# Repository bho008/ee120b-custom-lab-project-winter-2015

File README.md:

# ee120b-custom-lab-project-winter-2015
BACKUP EVERYTHING 

Brian Ho's EE120B Custom Lab Project Winter 2015
bho008@ucr.edu

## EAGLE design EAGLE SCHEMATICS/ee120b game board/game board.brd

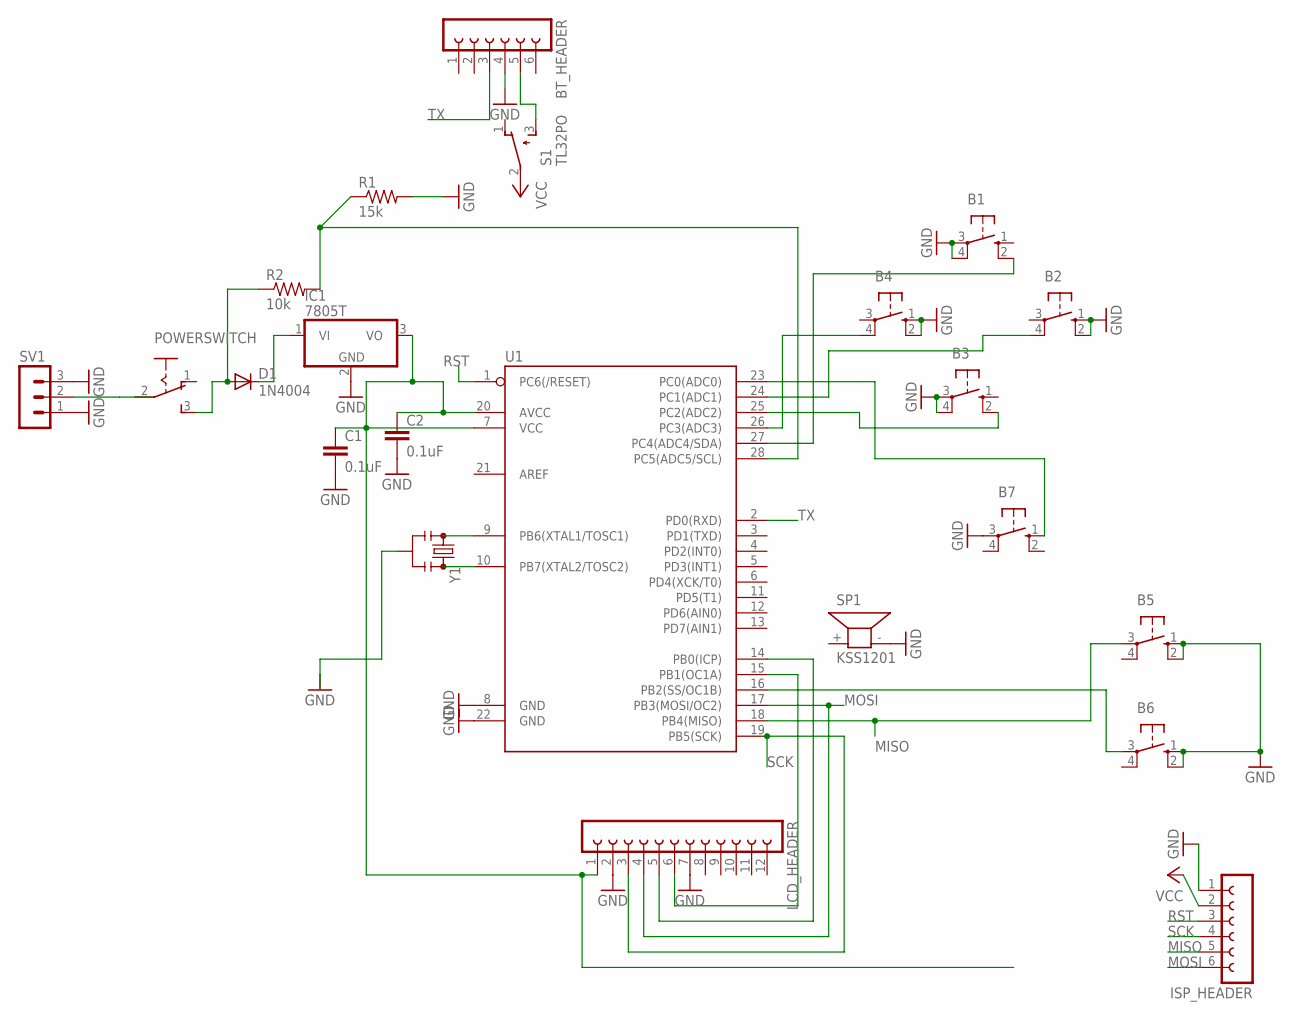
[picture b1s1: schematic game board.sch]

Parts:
B1, B2, B3, B4, B5, B6, B7: 10-XX; B3F-10XX
BT_HEADER: FE06W
C1, C2: 0.1uF; 0603-CAP
D1: 1N4004; DO41-10
IC1: 7805T; TO220H
ISP_HEADER: FE06W
LCD_HEADER: FE12W
POWERSWITCH: M251
R1: 15k; 0204/7
R2: 10k; 0204/7
S1: TL32PO; TL3XPO
SP1: KSS1201
SV1: MA03-1
U1: ATMEGA328P_PDIP; DIL28-3
Y1: RESONATORPTH; RESONATOR-PTH

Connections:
GND: B1.3, B1.4 (P1), B2.1 (S), B2.2 (S1), B3.3, B3.4 (P1), B4.1 (S), B4.2 (S1), B5.1 (S), B5.2 (S1), B6.1 (S), B6.2 (S1), B7.3, BT_HEADER.4, C1.2, C2.2, IC1.2 (GND), ISP_HEADER.1, LCD_HEADER.2, LCD_HEADER.7, R1.2, SP1.- (2), SV1.1, SV1.3, U1.8 (GND), U1.22 (GND), Y1.2
MISO: B5.3, ISP_HEADER.5, U1.18 (PB4(MISO))
MOSI: ISP_HEADER.6, LCD_HEADER.4, U1.17 (PB3(MOSI/OC2))
unnamed: D1.C, IC1.1 (VI)
unnamed: D1.A, POWERSWITCH.3 (S), R2.1
unnamed: R1.1, R2.2, U1.28 (PC5(ADC5/SCL))
unnamed: B7.1 (S), U1.23 (PC0(ADC0))
unnamed: B6.3, U1.16 (PB2(SS/OC1B))
unnamed: BT_HEADER.5, S1.3 (S)
unnamed: LCD_HEADER.5, U1.14 (PB0(ICP))
unnamed: B1.2 (S1), U1.27 (PC4(ADC4/SDA))
unnamed: U1.9 (PB6(XTAL1/TOSC1)), Y1.1
unnamed: U1.10 (PB7(XTAL2/TOSC2)), Y1.3
unnamed: B2.4 (P1), U1.24 (PC1(ADC1))
unnamed: B3.2 (S1), U1.25 (PC2(ADC2))
unnamed: POWERSWITCH.2, SV1.2
unnamed: LCD_HEADER.6, U1.15 (PB1(OC1A))
unnamed: B4.4 (P1), U1.26 (PC3(ADC3))
unnamed: C1.1, C2.1, IC1.3 (VO), LCD_HEADER.1, U1.7 (VCC), U1.20 (AVCC)
RST: ISP_HEADER.3, U1.1 (PC6(/RESET))
SCK: ISP_HEADER.4, LCD_HEADER.3, U1.19 (PB5(SCK))
TX: BT_HEADER.3, U1.2 (PD0(RXD))
VCC: ISP_HEADER.2, S1.2

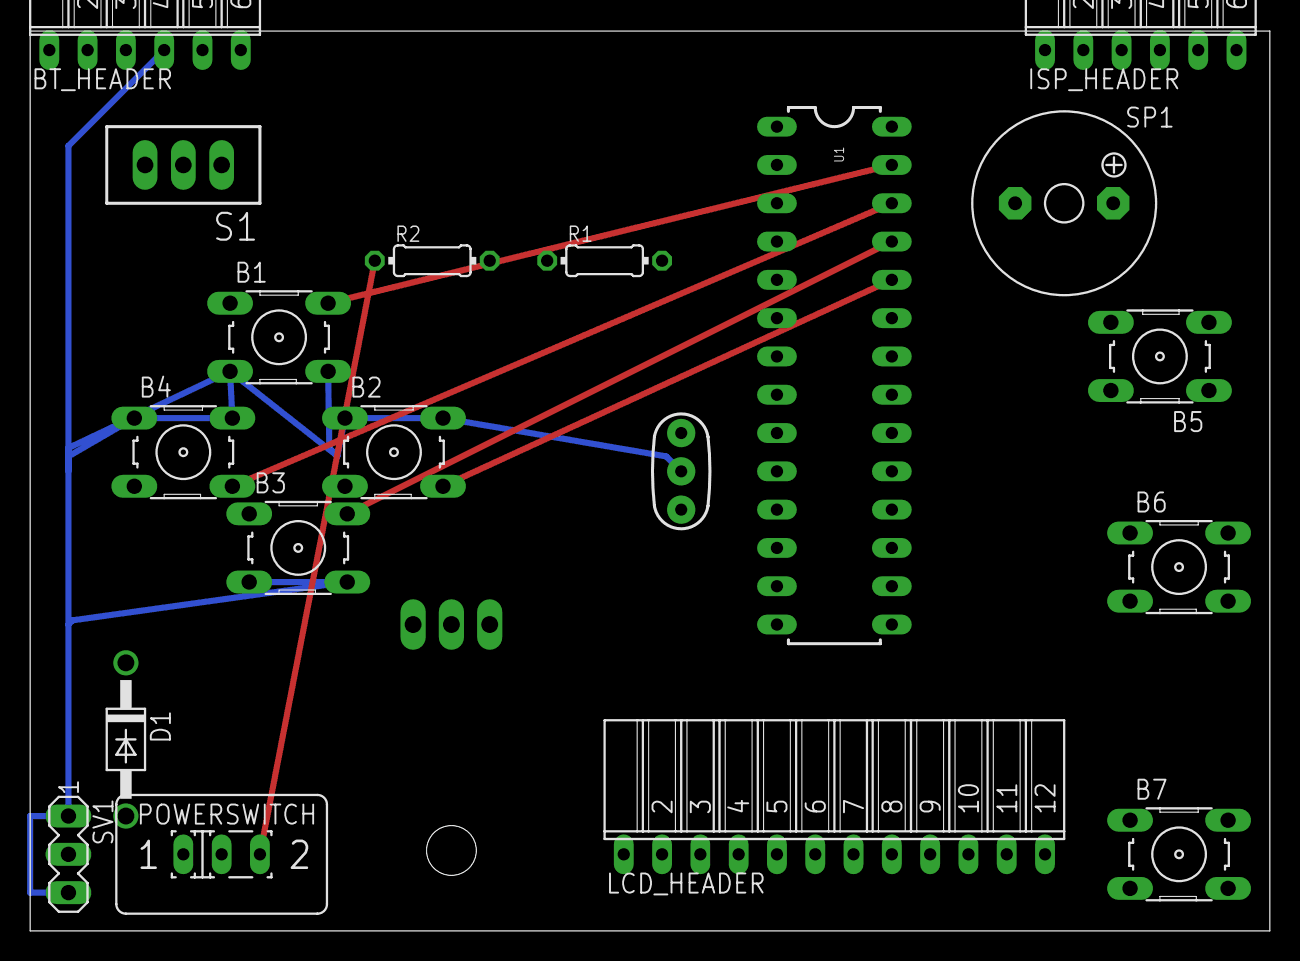
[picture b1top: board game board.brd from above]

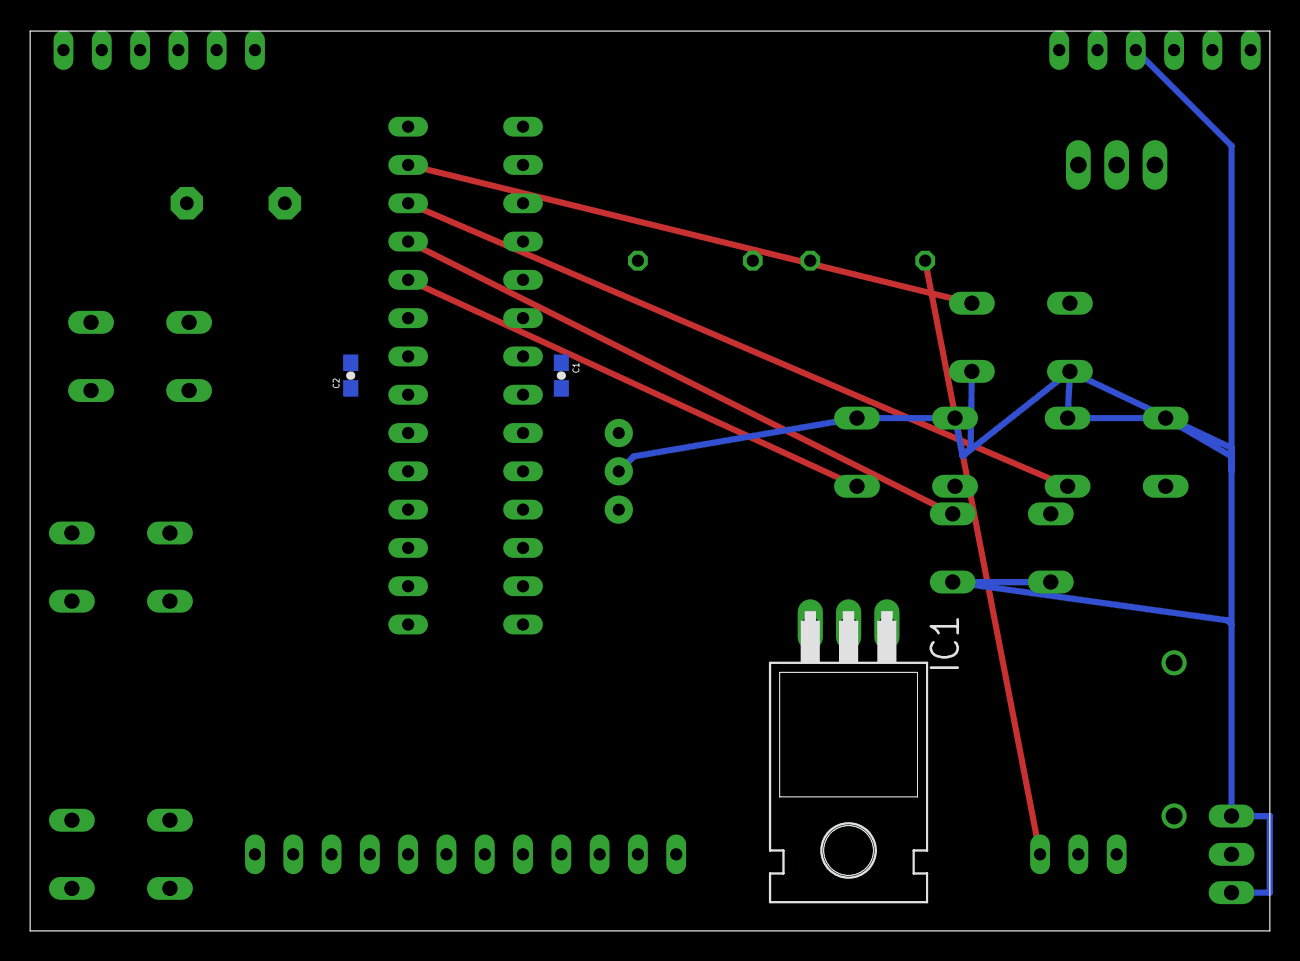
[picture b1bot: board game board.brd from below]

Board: 2 copper layers, 82.2 x 59.7 mm, 22 parts (3 on the bottom side), 23 nets.

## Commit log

2015-03-15 ee120b custom lab project winter 2015
    SNAKE GAME
2015-03-15 DUMP SOURCE HERE
2015-03-15 pics
2015-03-15 more pics

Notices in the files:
parts and their libraries:
SparkFun-Capacitors: Licensing: Creative Commons ShareAlike 4.0 International - https://creativecommons.org/licenses/by-sa/4.0
